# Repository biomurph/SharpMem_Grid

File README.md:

# SharpMem_Grid
Simple Board for the EOL SharpMem 96x96 LCD

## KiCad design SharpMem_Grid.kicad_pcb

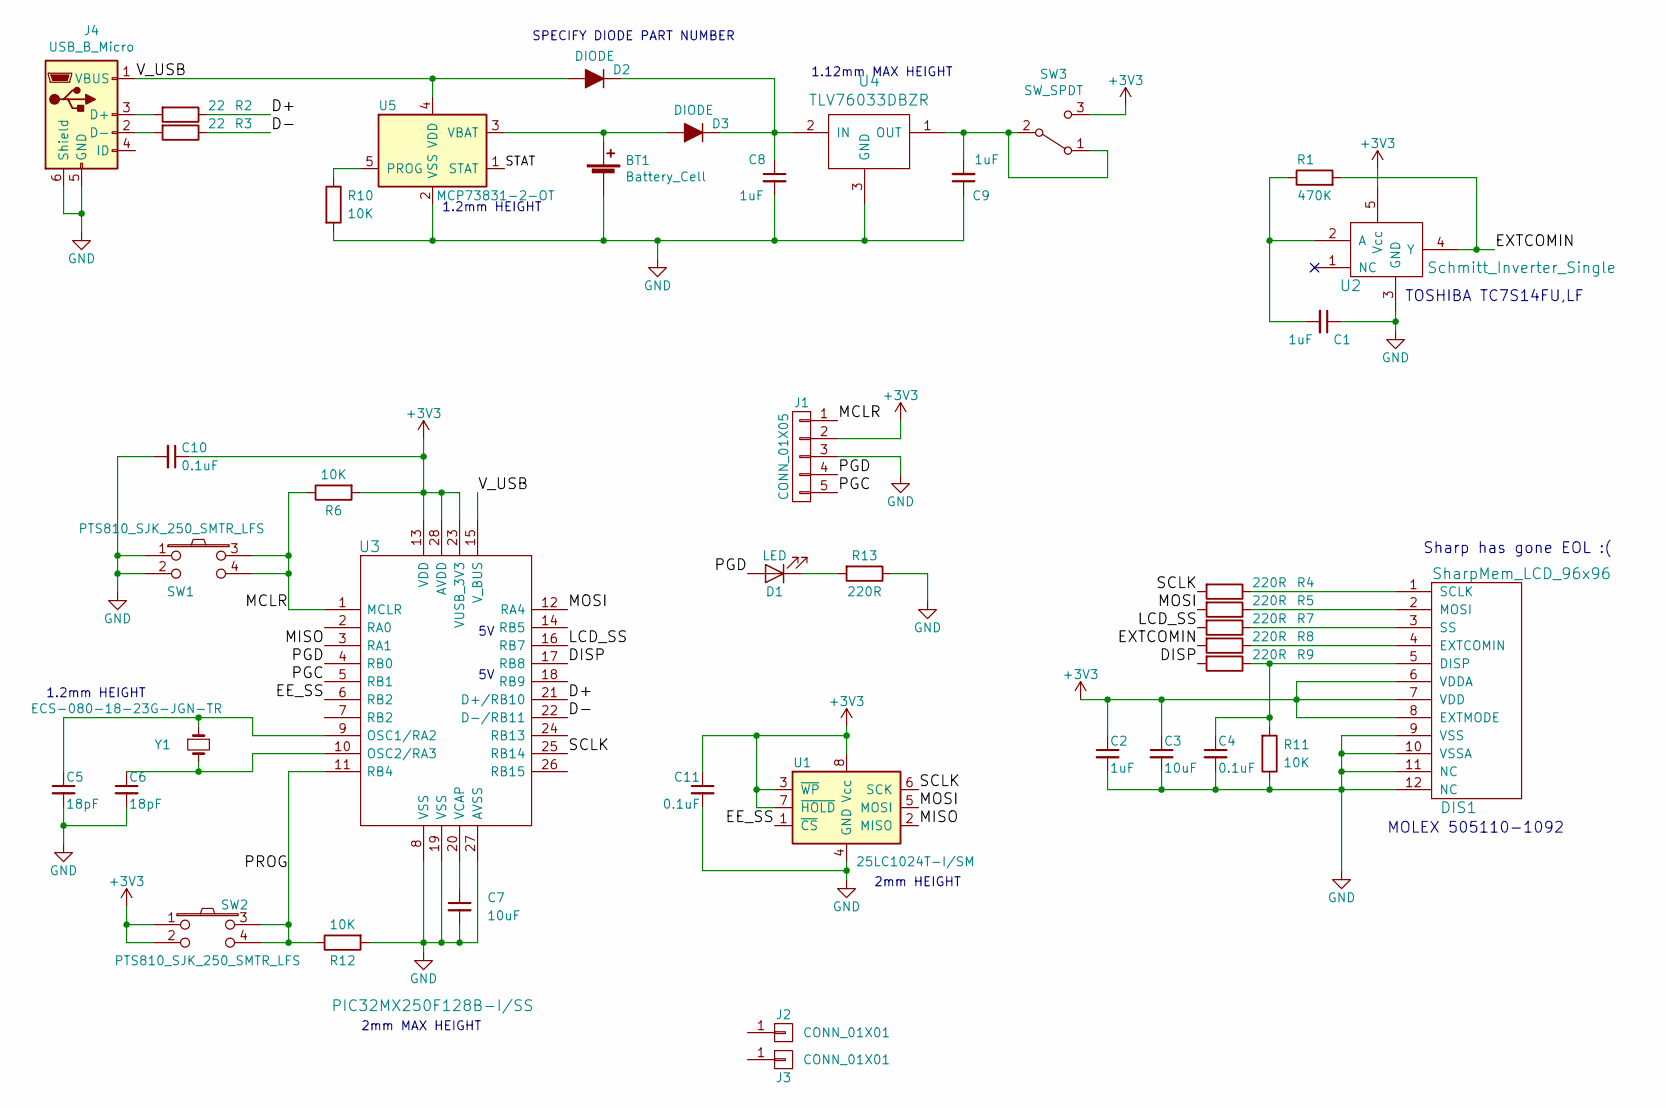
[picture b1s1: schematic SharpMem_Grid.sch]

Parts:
BT1: Battery_Cell; 4UCON-0217-20519
C1, C2, C8, C9: 1uF; C_0603
C3, C7: 10uF; C_0603
C4, C10, C11: 0.1uF; C_0603
C5, C6: 18pF; C_0603
D1: LED; C_0603
D2, D3: DIODE; D_0603
DIS1: SharpMem_LCD_96x96; MOLEX_505110-1092
J1: CONN_01X05; Pin_Header_Straight_1x05_Pitch2.00mm
J2, J3: CONN_01X01; MountingHole_3.2mm_M3
J4: USB_B_Micro; 10118193_microUSB
R1: 470K; C_0603
R2, R3: 22; C_0603
R4, R5, R7, R8, R9, R13: 220R; C_0603
R6, R10, R11, R12: 10K; C_0603
SW1, SW2: PTS810_SJK_250_SMTR_LFS; PTS810
SW3: SW_SPDT; SSSS810701_ALPS_SPDT
U1: 25LC1024T-I/SM; SOIJ-8_5.3x5.3mm_Pitch1.27mm
U2: Schmitt_Inverter_Single; SSOP-5-0.65_PITCH
U3: PIC32MX250F128B-I/SS; SSOP-28_5.3x10.2mm_Pitch0.65mm
U4: TLV76033DBZR; SOT-23
U5: MCP73831-2-OT; SOT-23-5
Y1: ECS-080-18-23G-JGN-TR; ECS-080-18-23G-JGN-TR_8MHz_60x35

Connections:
+3V3: C2.1, C3.1, C10.1, C11.1, DIS1.6 (VDDA), DIS1.7 (VDD), DIS1.8 (EXTMODE), J1.2, R6.2, SW2.1, SW2.2, SW3.3 (C), U1.3 (~WP), U1.7 (~HOLD), U1.8 (Vcc), U2.5 (Vcc), U3.13 (VDD), U3.23 (VUSB_3V3), U3.28 (AVDD)
/D+: R2.1, U3.21 (D+/RB10)
/D-: R3.1, U3.22 (D-/RB11)
/DISP: R9.2, U3.17 (RB8)
/EE_SS: U1.1 (~CS), U3.6 (RB2)
/EXTCOMIN: R1.2, R8.2, U2.4 (Y)
/LCD_SS: R7.2, U3.16 (RB7)
/MCLR: J1.1, R6.1, SW1.3, SW1.4, U3.1 (MCLR)
/MISO: U1.2 (MISO), U3.3 (RA1)
/MOSI: R5.2, U1.5 (MOSI), U3.12 (RA4)
/PGC: J1.5, U3.5 (RB1)
/PGD: D1.2 (A), J1.4, U3.4 (RB0)
/PROG: R12.1, SW2.3, SW2.4, U3.11 (RB4)
/SCLK: R4.2, U1.6 (SCK), U3.25 (RB14)
/STAT: U5.1 (STAT)
/V_USB: D2.2 (A), J4.1 (VBUS), U3.15 (V_BUS), U5.4 (VDD)
GND: BT1.2 (-), BT1.3, BT1.4, C1.1, C2.2, C3.2, C4.2, C5.2, C6.2, C7.2, C8.2, C9.1, C10.2, C11.2, DIS1.9 (VSS), DIS1.10 (VSSA), DIS1.11 (NC), DIS1.12 (NC), J1.3, J4.5 (GND), J4.6 (Shield), J4.7, J4.8, J4.9, J4.10, J4.11, R10.2, R11.1, R12.2, R13.1, SW1.1, SW1.2, U1.4 (GND), U2.3 (GND), U3.8 (VSS), U3.19 (VSS), U3.27 (AVSS), U4.3 (GND), U5.2 (VSS)
unnamed: BT1.1 (+), D3.2 (A), U5.3 (VBAT)
unnamed: C1.2, R1.1, U2.2 (A)
unnamed: C4.1, DIS1.5 (DISP), R9.1, R11.2
unnamed: C5.1, U3.9 (OSC1/RA2), Y1.1
unnamed: C6.1, U3.10 (OSC2/RA3), Y1.2
unnamed: C7.1, U3.20 (VCAP)
unnamed: C8.1, D2.1 (K), D3.1 (K), U4.2 (IN)
unnamed: C9.2, SW3.1 (A), SW3.2 (B), U4.1 (OUT)
unnamed: D1.1 (K), R13.2
unnamed: DIS1.1 (SCLK), R4.1
unnamed: DIS1.2 (MOSI), R5.1
unnamed: DIS1.3 (SS), R7.1
unnamed: DIS1.4 (EXTCOMIN), R8.1
unnamed: J4.2 (D-), R3.2
unnamed: J4.3 (D+), R2.2
unnamed: R10.1, U5.5 (PROG)

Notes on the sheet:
TOSHIBA TC7S14FU,LF
Sharp has gone EOL :(
MOLEX 505110-1092
5V 5V
SPECIFY DIODE PART NUMBER
2mm MAX HEIGHT
1.2mm HEIGHT
1.12mm MAX HEIGHT
2mm HEIGHT

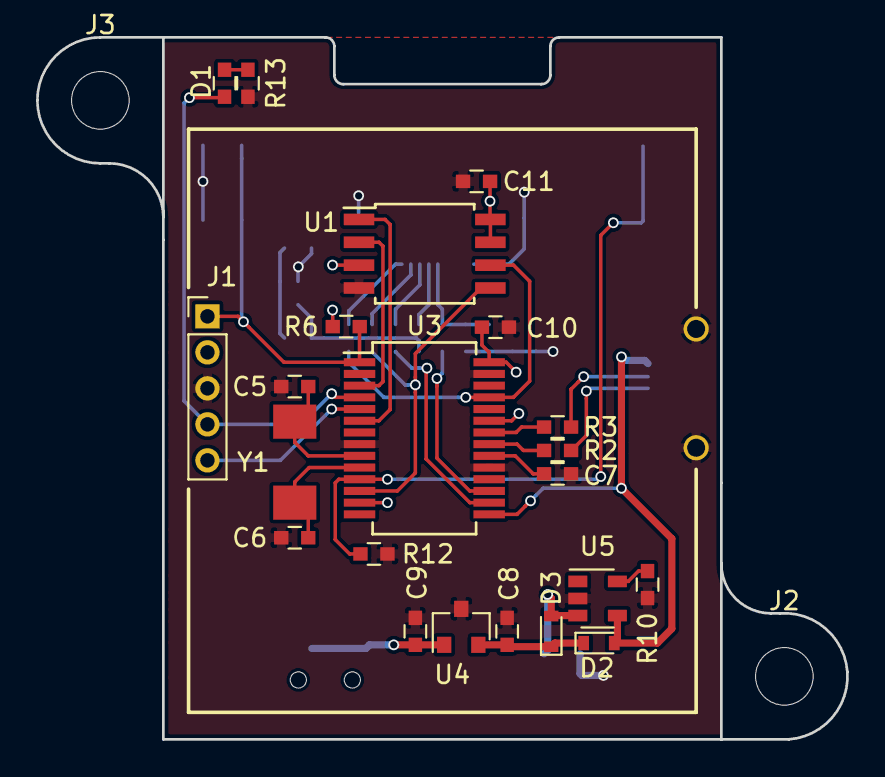
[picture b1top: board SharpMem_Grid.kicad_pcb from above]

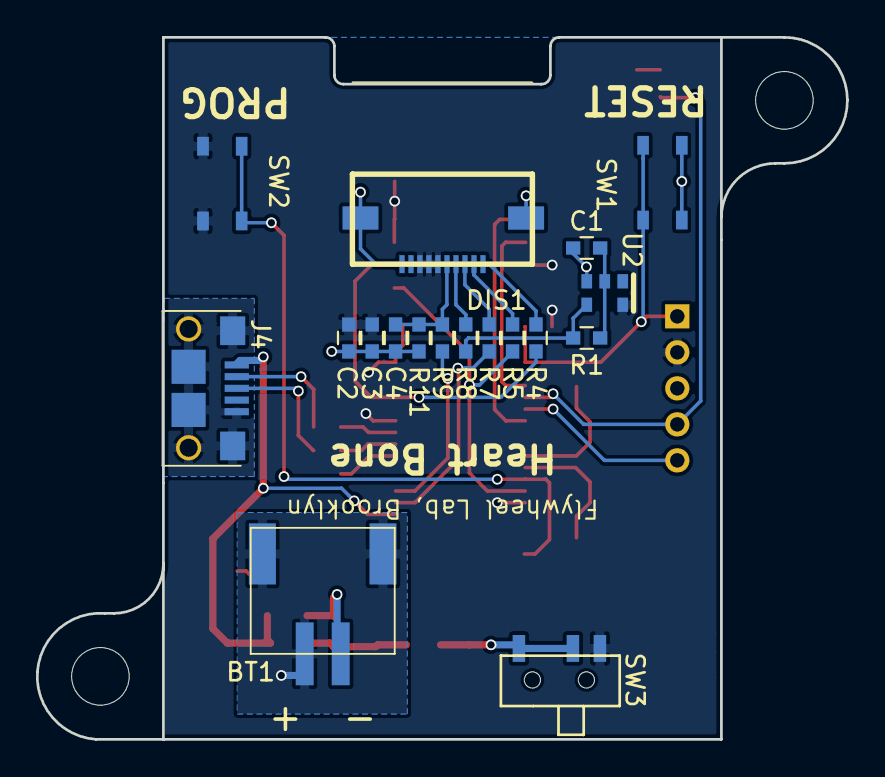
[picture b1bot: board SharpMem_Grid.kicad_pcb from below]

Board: 2 copper layers, 38.0 x 39.0 mm, 42 parts (18 on the bottom side), 32 nets.

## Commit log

2018-08-27 Annotated and associated footprints
2018-08-27 Moved Library and updated paths
2018-08-28 Laid out the schematic
2018-08-28 ASSOCIATED FOOTPRINTS
2018-08-29 Lay out components
2018-09-01 Routed traces and copper pour. Passes DFM
2018-09-02 Final layout and BOM
2019-05-24 redesighn for itp camp
2019-05-24 board layout and routing passing DRC
2019-05-28 dusting up and moving to new repo
2020-06-15 schematic
